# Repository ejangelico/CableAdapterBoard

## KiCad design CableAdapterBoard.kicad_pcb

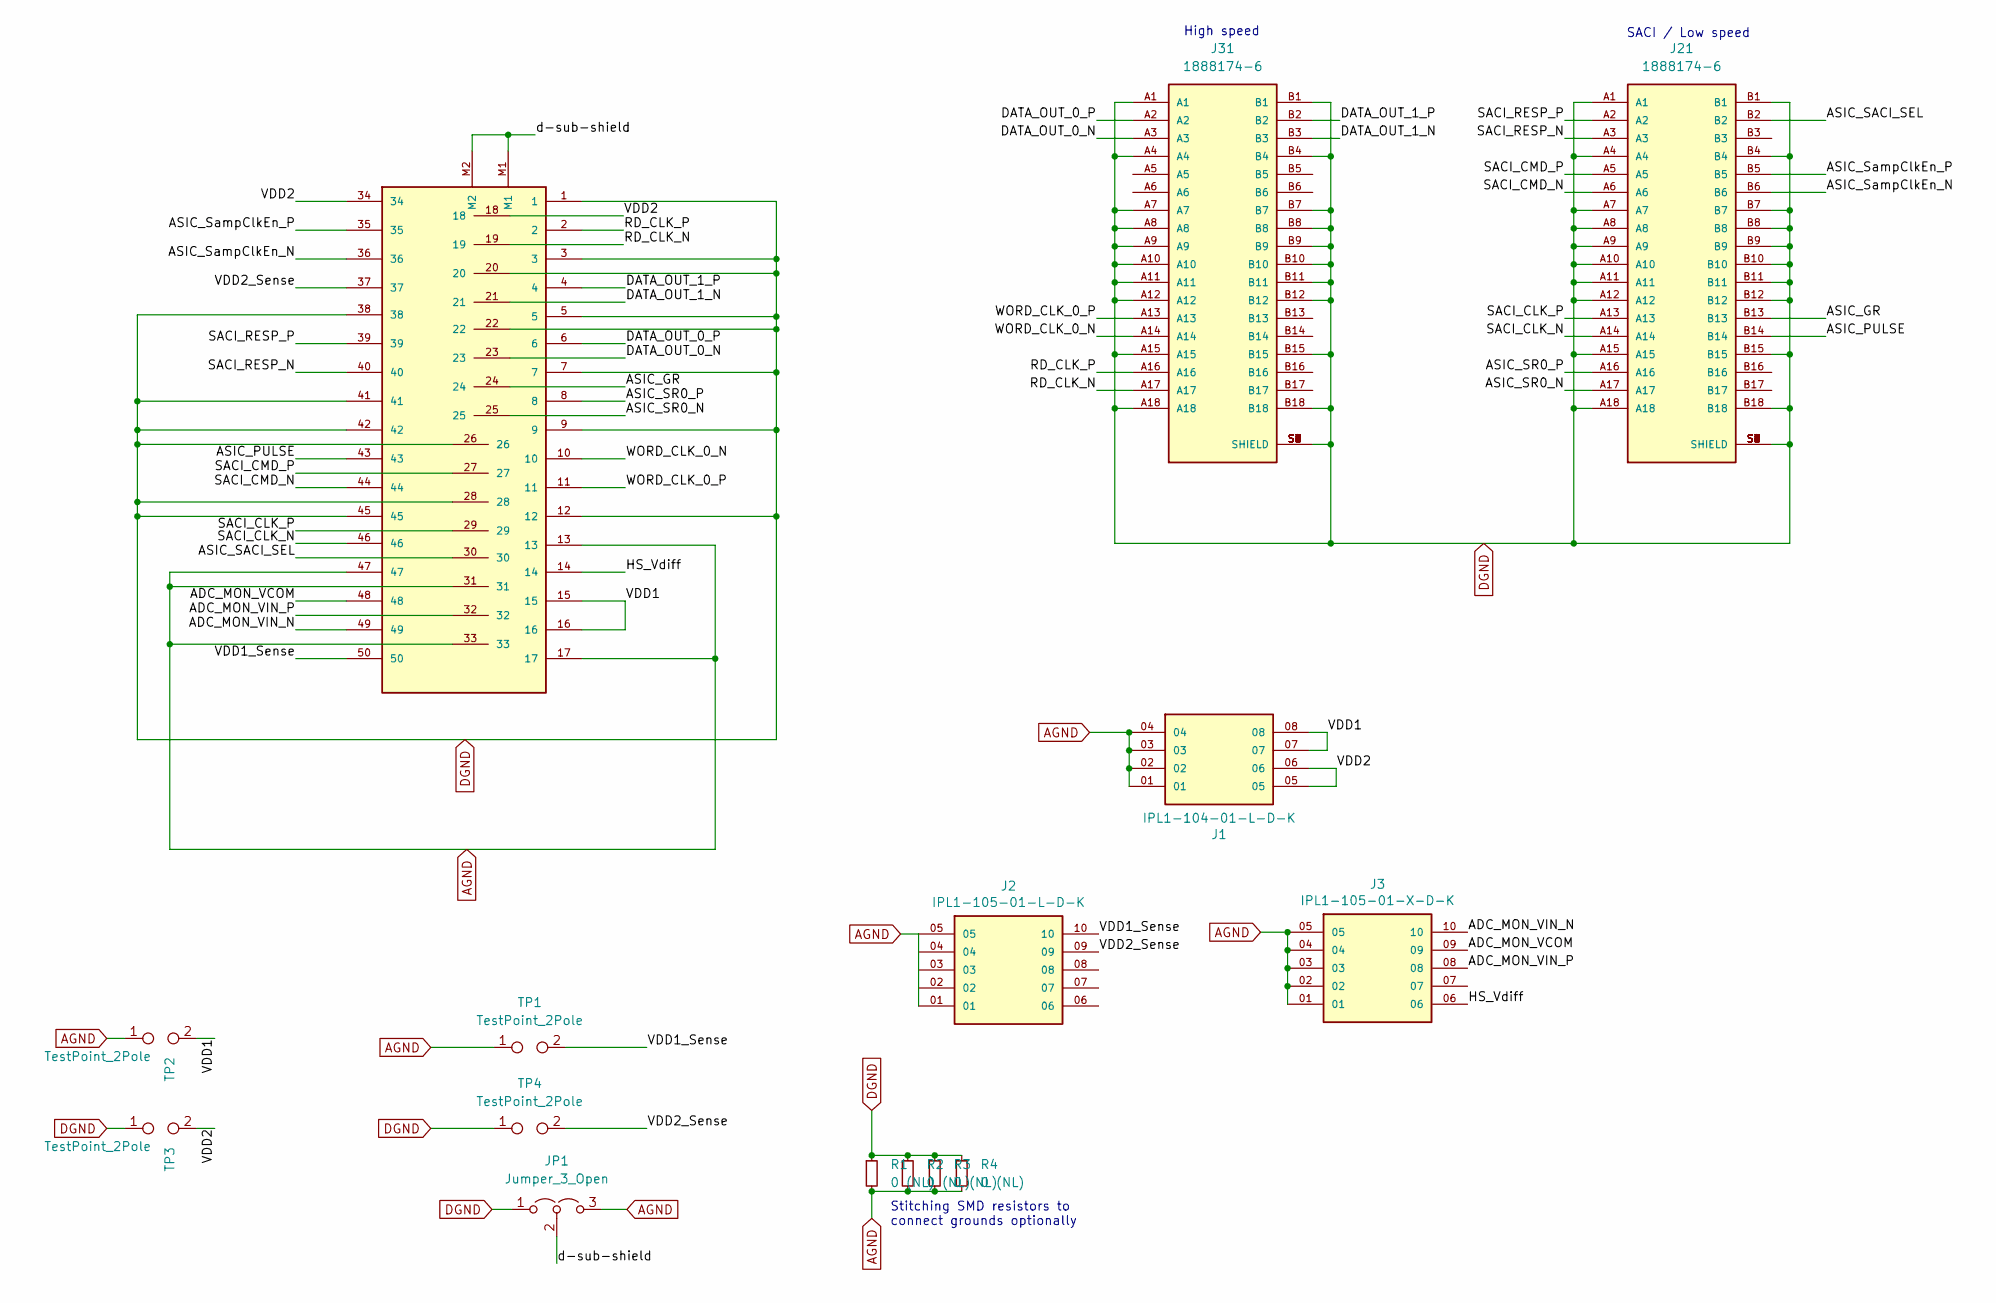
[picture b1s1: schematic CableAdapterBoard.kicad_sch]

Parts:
DSUB1: 5747193-2; SKT-50
J1: IPL1-104-01-L-D-K; SAMTEC_IPL1-104-01-L-D-K; PARTREV E
J2: IPL1-105-01-L-D-K; SAMTEC_IPL1-105-01-X-D-K; PARTREV E
J3: IPL1-105-01-X-D-K; SAMTEC_IPL1-105-01-X-D-K; PARTREV E
J21, J31: 1888174-6; TE_1888174-6
JP1: Jumper_3_Open; PinHeader_1x03_P2.54mm_Vertical
R1, R2, R3, R4: 0 (NL); R_0805_2012Metric_Pad1.20x1.40mm_HandSolder
TP1, TP2, TP3, TP4: TestPoint_2Pole; TestPoint_2Pads_Pitch5.08mm_Drill1.3mm

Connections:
/ADC_MON_VCOM: DSUB1.48, J3.09
/ADC_MON_VIN_N: DSUB1.49, J3.10
/ADC_MON_VIN_P: DSUB1.32, J3.08
/ASIC_GR: DSUB1.24, J21.B13
/ASIC_PULSE: DSUB1.43, J21.B14
/ASIC_SACI_SEL: DSUB1.30, J21.B2
/ASIC_SR0_N: DSUB1.25, J21.A17
/ASIC_SR0_P: DSUB1.8, J21.A16
/ASIC_SampClkEn_N: DSUB1.36, J21.B6
/ASIC_SampClkEn_P: DSUB1.35, J21.B5
/DATA_OUT_0_N: DSUB1.23, J31.A3
/DATA_OUT_0_P: DSUB1.6, J31.A2
/DATA_OUT_1_N: DSUB1.21, J31.B3
/DATA_OUT_1_P: DSUB1.4, J31.B2
/HS_Vdiff: DSUB1.14, J3.06
/RD_CLK_N: DSUB1.19, J31.A17
/RD_CLK_P: DSUB1.2, J31.A16
/SACI_CLK_N: DSUB1.46, J21.A14
/SACI_CLK_P: DSUB1.29, J21.A13
/SACI_CMD_N: DSUB1.44, J21.A6
/SACI_CMD_P: DSUB1.27, J21.A5
/SACI_RESP_N: DSUB1.40, J21.A3
/SACI_RESP_P: DSUB1.39, J21.A2
/VDD1: DSUB1.15, DSUB1.16, J1.07, J1.08, TP2.2
/VDD1_Sense: DSUB1.50, J2.10, TP1.2
/VDD2: DSUB1.18, DSUB1.34, J1.05, J1.06, TP3.2
/VDD2_Sense: DSUB1.37, J2.09, TP4.2
/WORD_CLK_0_N: DSUB1.10, J31.A14
/WORD_CLK_0_P: DSUB1.11, J31.A13
/d-sub-shield: DSUB1.M1, DSUB1.M2, JP1.2 (C)
AGND: DSUB1.13, DSUB1.17, DSUB1.31, DSUB1.33, DSUB1.47, J1.01, J1.02, J1.03, J1.04, J2.01, J2.05, J3.01, J3.02, J3.03, J3.04, J3.05, JP1.3 (B), R1.2, R2.2, R3.2, R4.2, TP1.1, TP2.1
DGND: DSUB1.1, DSUB1.3, DSUB1.5, DSUB1.7, DSUB1.9, DSUB1.12, DSUB1.20, DSUB1.22, DSUB1.26, DSUB1.28, DSUB1.38, DSUB1.41, DSUB1.42, DSUB1.45, J21.A1, J21.A4, J21.A7, J21.A8, J21.A9, J21.A10, J21.A11, J21.A12, J21.A15, J21.A18, J21.B1, J21.B4, J21.B7, J21.B8, J21.B9, J21.B10, J21.B11, J21.B12, J21.B15, J21.B18, J21.S1 (SHIELD), J21.S2 (SHIELD), J21.S3 (SHIELD), J21.S4 (SHIELD), J21.S5 (SHIELD), J21.S6 (SHIELD), J21.S7 (SHIELD), J21.S8 (SHIELD), J31.A1, J31.A4, J31.A7, J31.A8, J31.A9, J31.A10, J31.A11, J31.A12, J31.A15, J31.A18, J31.B1, J31.B4, J31.B7, J31.B8, J31.B9, J31.B10, J31.B11, J31.B12, J31.B15, J31.B18, J31.S1 (SHIELD), J31.S2 (SHIELD), J31.S3 (SHIELD), J31.S4 (SHIELD), J31.S5 (SHIELD), J31.S6 (SHIELD), J31.S7 (SHIELD), J31.S8 (SHIELD), JP1.1 (A), R1.1, R2.1, R3.1, R4.1, TP3.1, TP4.1

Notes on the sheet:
Stitching SMD resistors to connect grounds optionally
High speed
SACI / Low speed

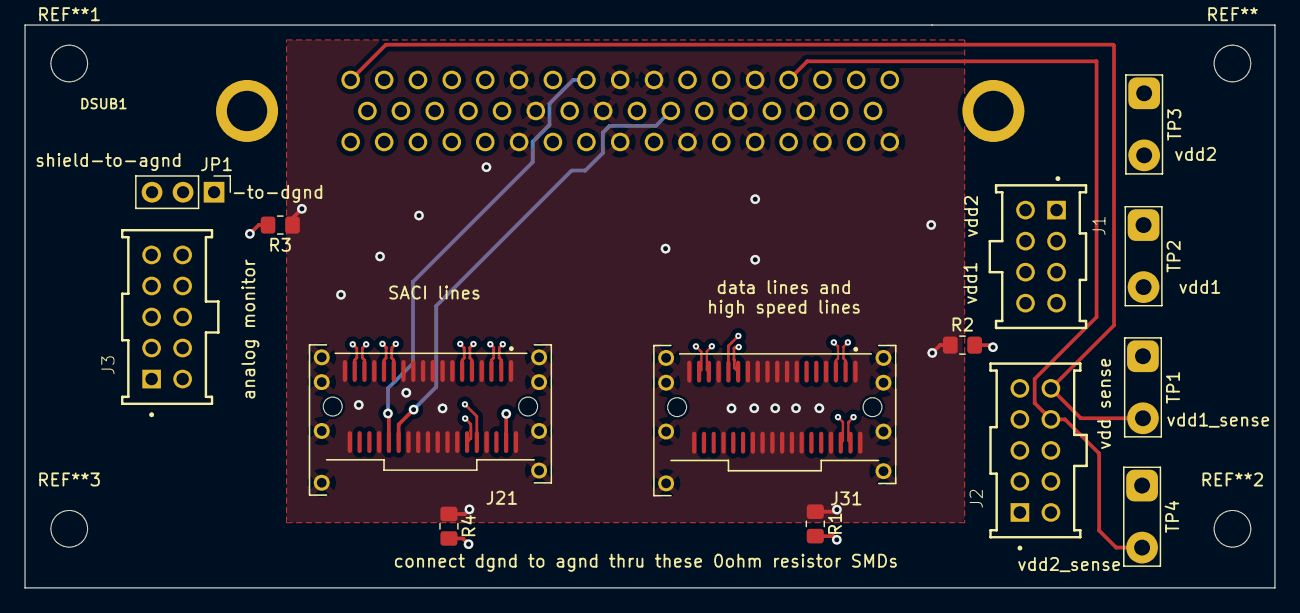
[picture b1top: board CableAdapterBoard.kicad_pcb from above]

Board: 6 copper layers, 102.3 x 46.1 mm, 15 parts (0 on the bottom side), 32 nets.

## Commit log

2023-08-28 As produced in July 2023
2023-10-12 Backups, about to make a feature change
2023-10-12 Changed orientation of 36 pin minisas connectors to be CORRECT. old version needed a flip due to always top-to-bottom crossover format of these cables. corrected some labeling.
2025-08-01 SOme backups and gerbers
